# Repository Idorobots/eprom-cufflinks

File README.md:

# EPROM Cufflinks
Maybe it's Maybelline, maybe it's just nerdy.

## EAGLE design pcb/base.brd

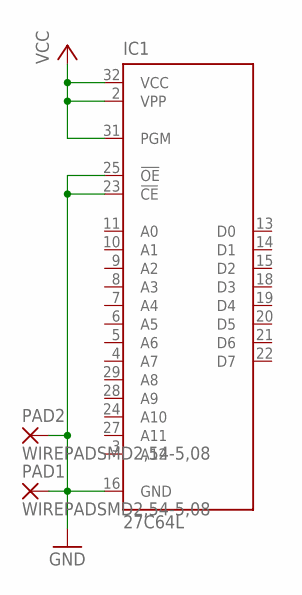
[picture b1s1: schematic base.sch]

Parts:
IC1: 27C64L; PLCC-32
PAD1, PAD2: WIREPADSMD2,54-5,08; SMD2,54-5,08

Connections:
GND: IC1.16 (GND), IC1.23 (!CE), IC1.25 (!OE), PAD1.1, PAD2.1
VCC: IC1.2 (VPP), IC1.31 (PGM), IC1.32 (VCC)

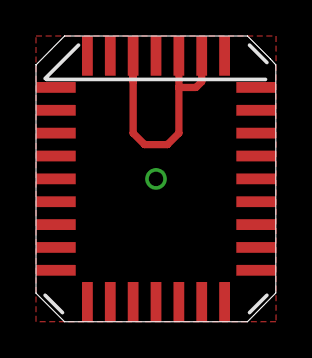
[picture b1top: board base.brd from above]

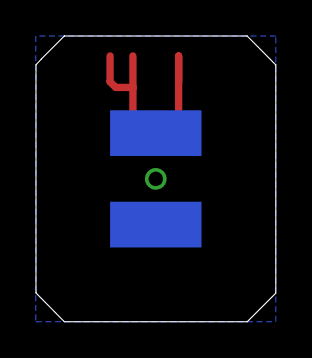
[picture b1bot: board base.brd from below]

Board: 2 copper layers, 13.3 x 15.9 mm, 3 parts (2 on the bottom side), 2 nets.

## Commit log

2016-05-07 Added the PCB layout.
2016-05-07 Changed mounting pad for the cufflink back.
2016-05-07 Connected the rest of the pins.
2016-05-09 Added a picture of the finished cufflinks.
